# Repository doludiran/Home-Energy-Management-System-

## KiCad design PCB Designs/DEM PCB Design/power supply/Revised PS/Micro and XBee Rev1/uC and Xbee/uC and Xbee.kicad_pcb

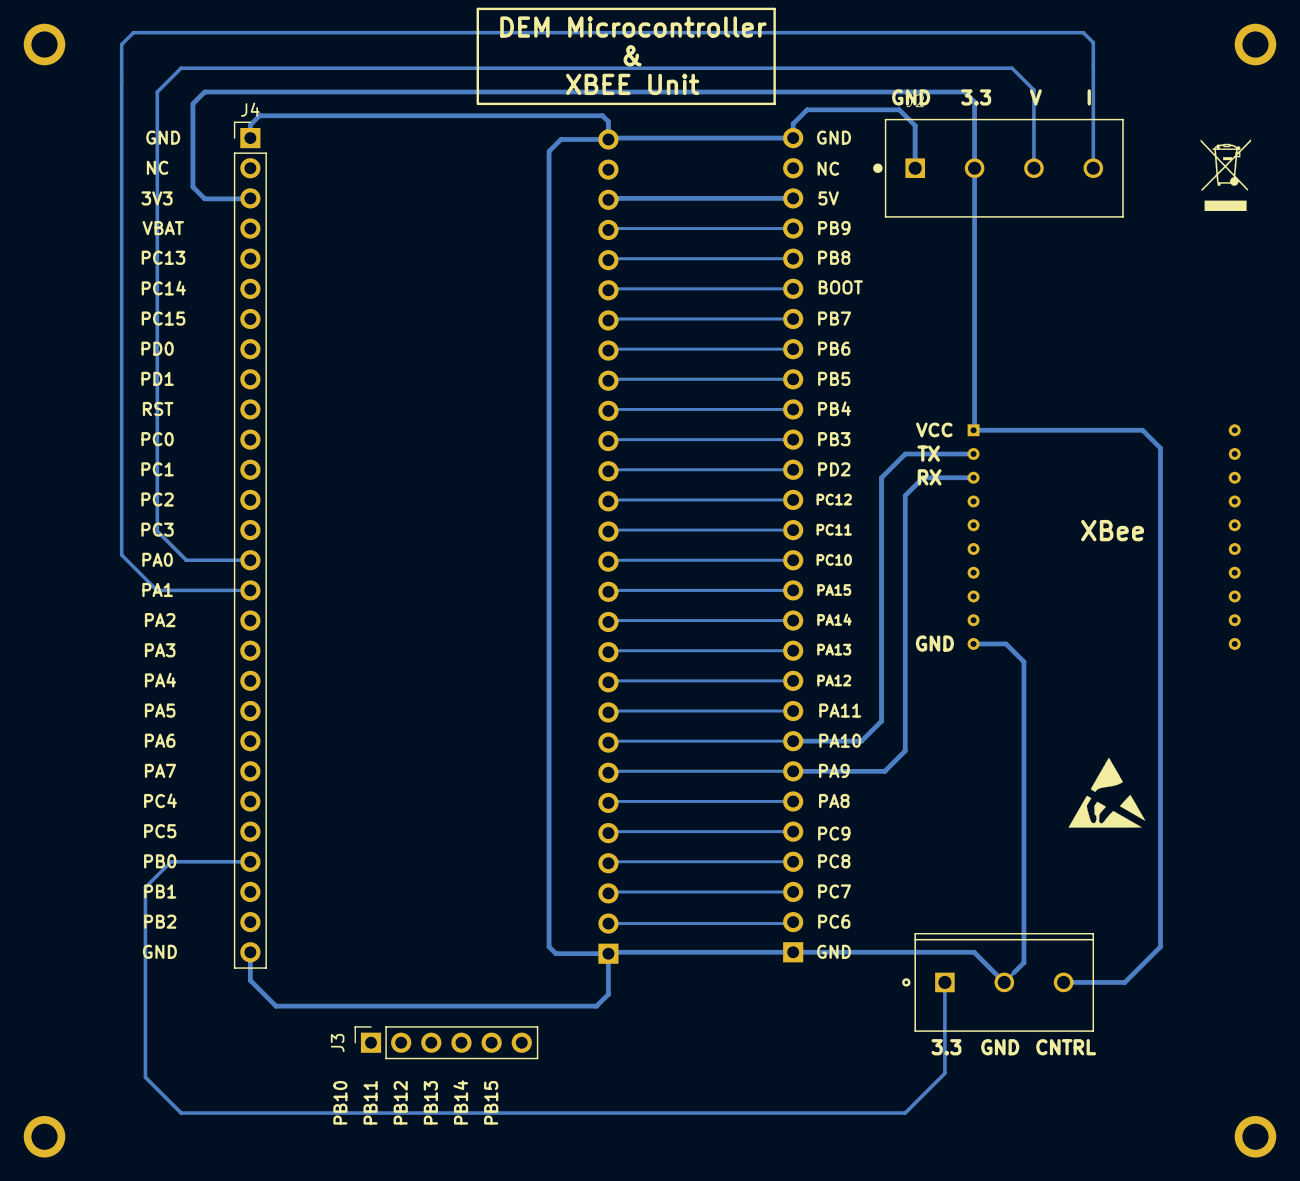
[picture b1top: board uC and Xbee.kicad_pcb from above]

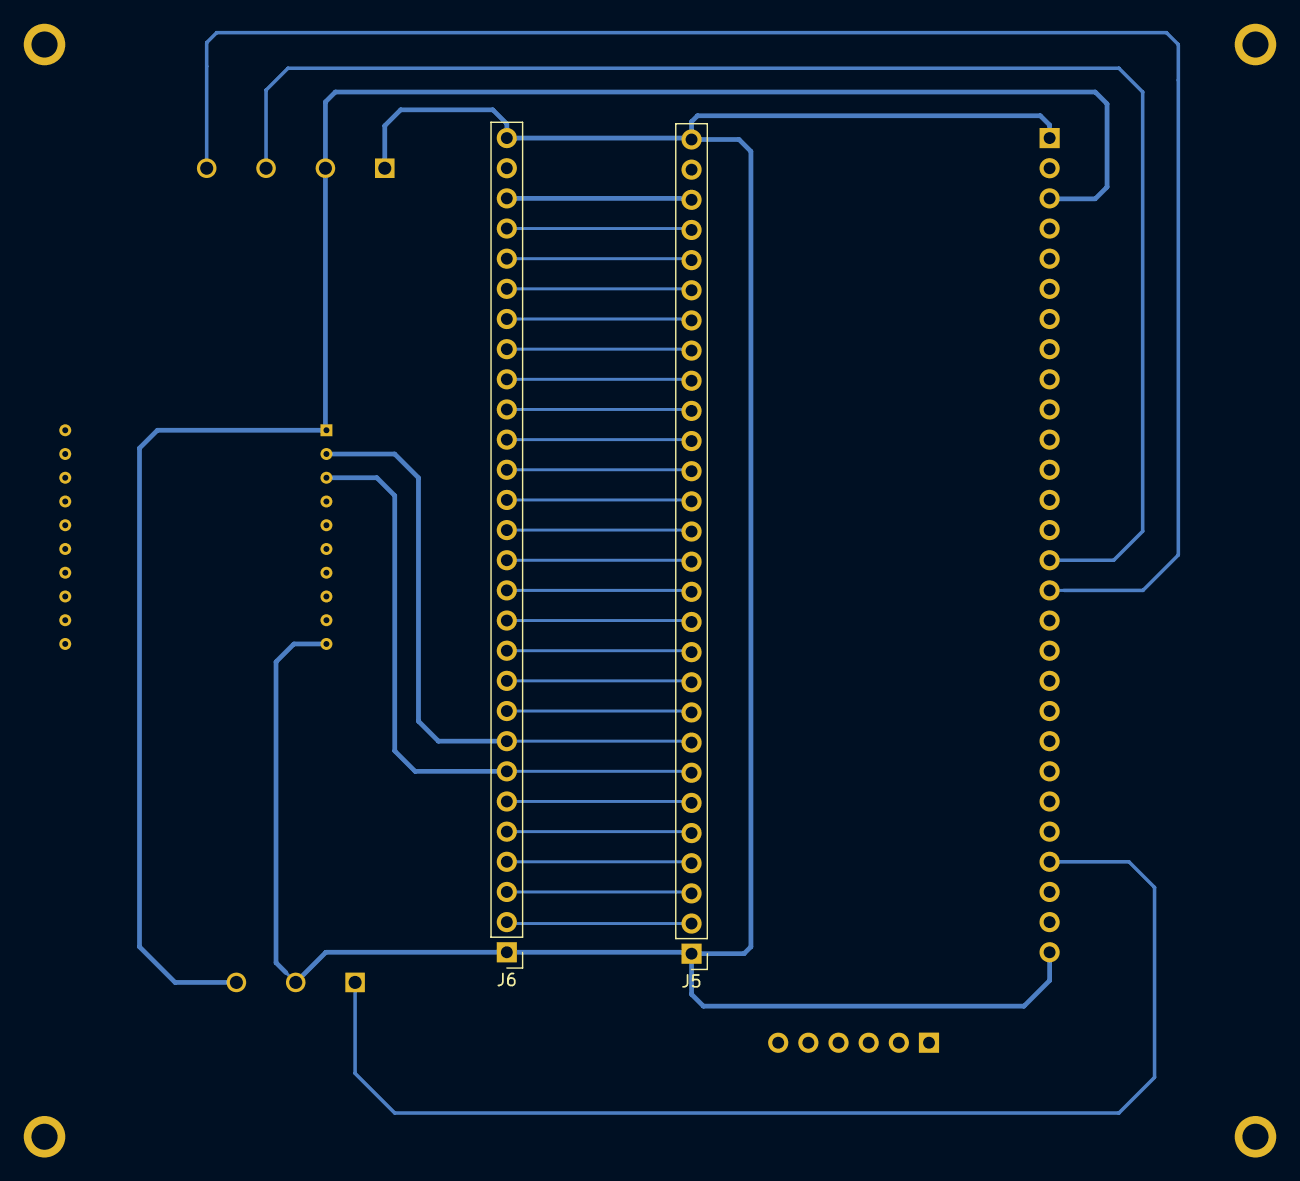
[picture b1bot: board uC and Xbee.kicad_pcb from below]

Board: 2 copper layers, 7 parts (2 on the bottom side), 30 nets.

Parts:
J1: 282836-3; TE_282836-3
J2: 282836-4; TE_282836-4
J3: Conn_01x06_Female; PinSocket_1x06_P2.54mm_Vertical
J4, J5, J6: Conn_01x28_Female; PinHeader_1x28_P2.54mm_Vertical
U1: XB24CDMSIT-001; DIP-20

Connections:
3.3V1: J1.3, J2.2, J4.3, U1.1
5V: J5.26, J6.26
BOOT: J5.23, J6.23
GND1: J1.2, J2.1, J4.1, J4.28, J5.1, J5.28, J6.1, J6.28, U1.10
PA0: J2.3, J4.15
PA1: J2.4, J4.16
PA8: J5.6, J6.6
PA9: J5.7, J6.7, U1.3
PA10: J5.8, J6.8, U1.2
PA11: J5.9, J6.9
PA12: J5.10, J6.10
PA13: J5.11, J6.11
PA14: J5.12, J6.12
PA15: J5.13, J6.13
PB0: J1.1, J4.25
PB3: J5.18, J6.18
PB4: J5.19, J6.19
PB5: J5.20, J6.20
PB6: J5.21, J6.21
PB7: J5.22, J6.22
PB8: J5.24, J6.24
PB9: J5.25, J6.25
PC6: J5.2, J6.2
PC7: J5.3, J6.3
PC8: J5.4, J6.4
PC9: J5.5, J6.5
PC10: J5.14, J6.14
PC11: J5.15, J6.15
PC12: J5.16, J6.16
PD2: J5.17, J6.17

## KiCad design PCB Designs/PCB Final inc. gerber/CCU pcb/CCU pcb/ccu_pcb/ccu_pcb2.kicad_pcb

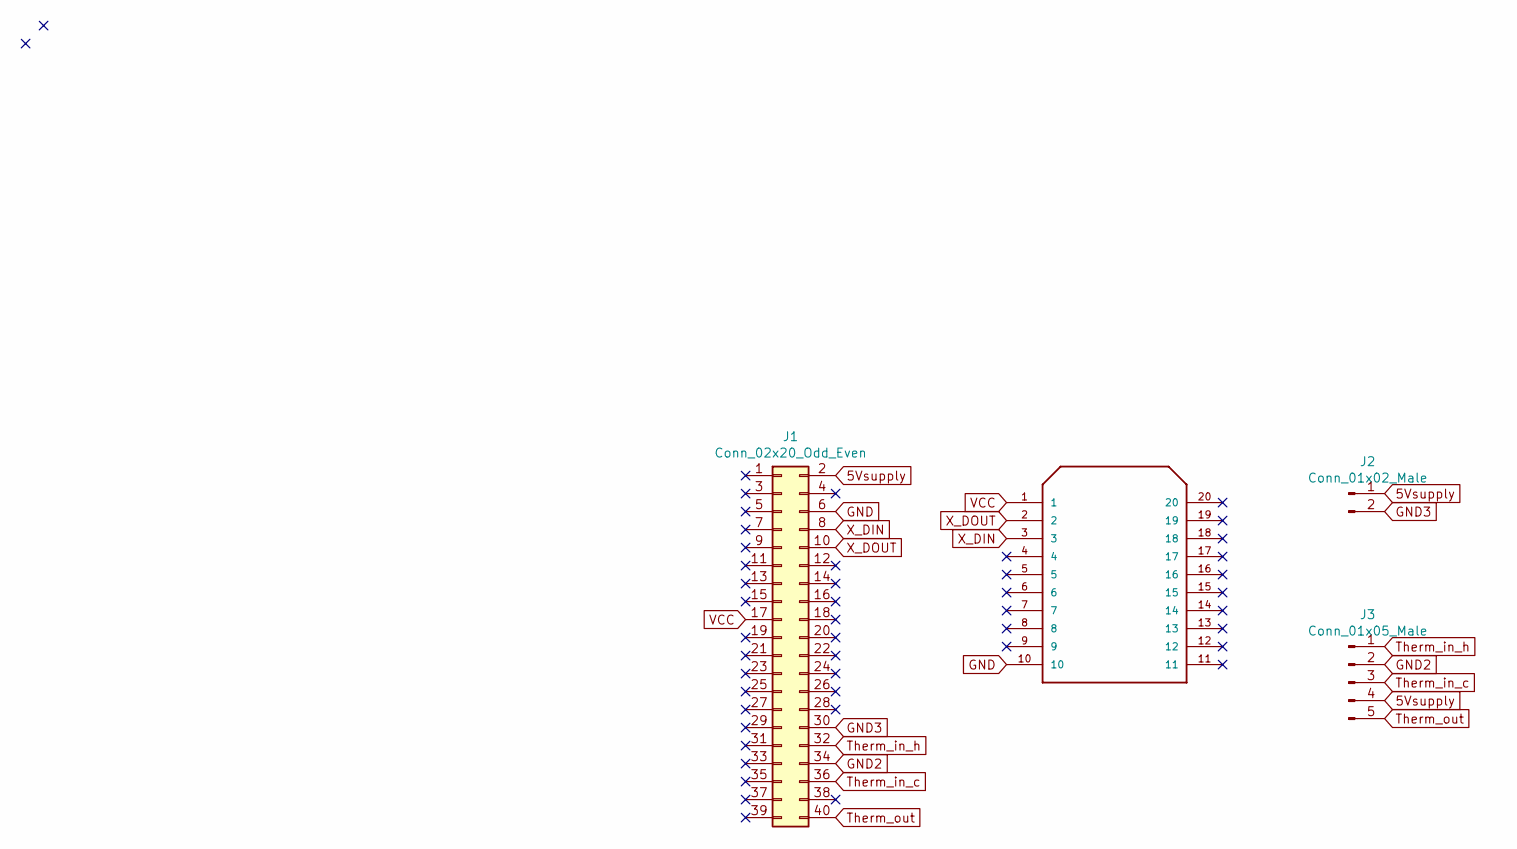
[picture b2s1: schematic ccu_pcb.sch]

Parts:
J1: Conn_02x20_Odd_Even; PinHeader_2x20_P2.54mm_Vertical
J2: Conn_01x02_Male; PinHeader_1x02_P2.54mm_Vertical
J3: Conn_01x05_Male; PinHeader_1x05_P2.54mm_Vertical
U1: XB24CDMPIT-001; DIP-20

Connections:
5Vsupply: J1.2, J2.1, J3.4
GND: J1.6, U1.10
GND2: J1.34, J3.2
GND3: J1.30, J2.2
Therm_in_c: J1.36, J3.3
Therm_in_h: J1.32, J3.1
Therm_out: J1.40, J3.5
VCC: J1.17, U1.1
X_DIN: J1.8, U1.3
X_DOUT: J1.10, U1.2

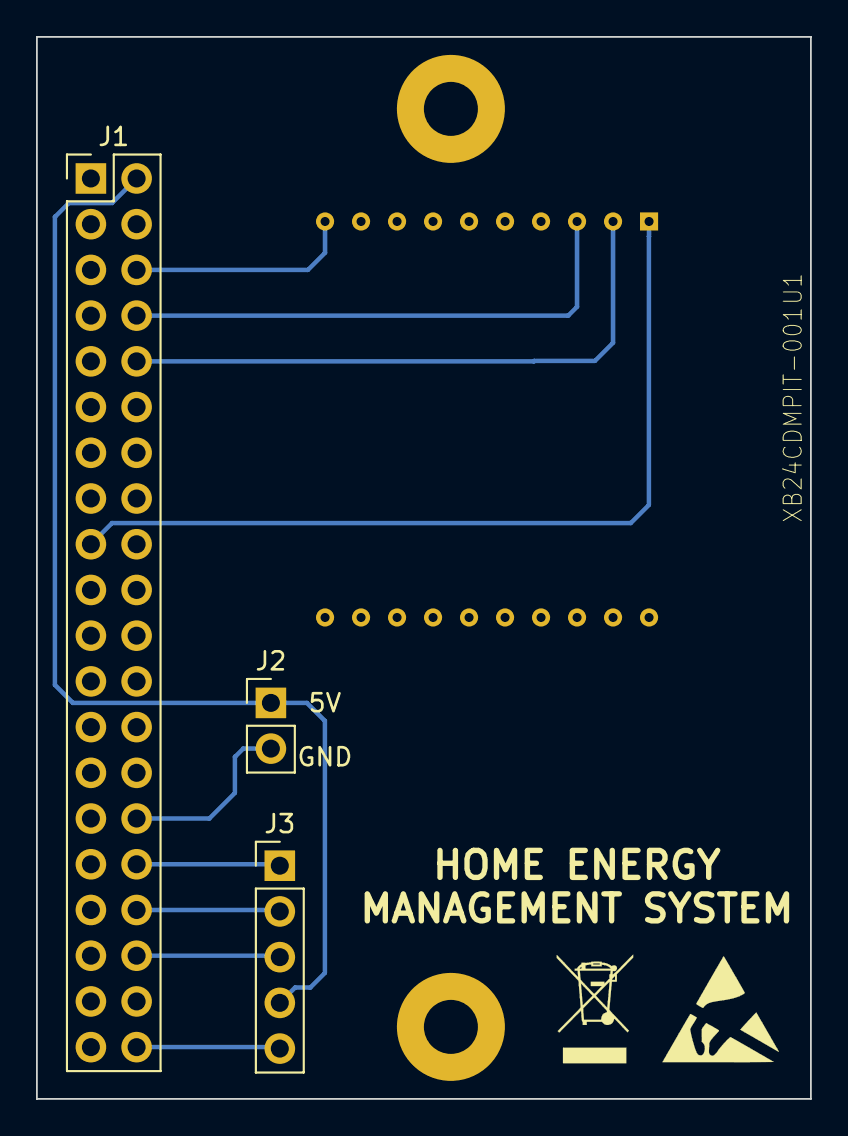
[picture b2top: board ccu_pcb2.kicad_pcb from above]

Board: 2 copper layers, 43.0 x 59.0 mm, 4 parts (0 on the bottom side), 10 nets.

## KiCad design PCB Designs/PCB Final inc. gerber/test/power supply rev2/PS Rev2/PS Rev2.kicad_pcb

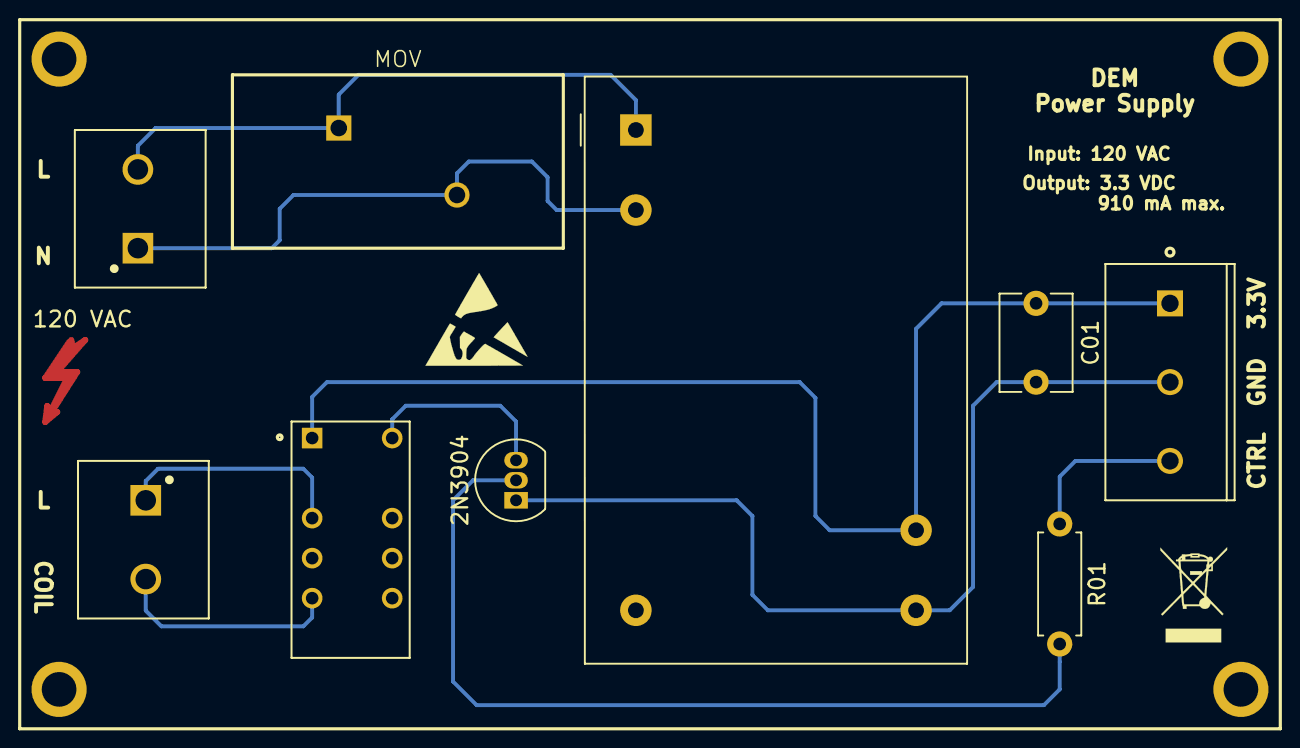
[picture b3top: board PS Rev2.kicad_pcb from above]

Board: 2 copper layers, 10 parts (0 on the bottom side), 9 nets.

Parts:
2N3904: 2N3904; TO-92_Inline
120 VAC : Symbol_Highvoltage_Type1_CopperTop_Small
C01: 400 nF; C_Disc_D6.0mm_W4.4mm_P5.00mm
J01, J03: 1935161; PHOENIX_1935161
J02: 282836-3; TE_282836-3
K01: EC2-3NU; KEMET_EC2-3NU
MOV: TMOV20RP300E; CAPRR750W81L2100T1100H2300P
PS01: RAC03-3.3SGA; Converter_ACDC_RECOM_RAC04-xxSGx_THT
R01: 10k; R_Axial_DIN0207_L6.3mm_D2.5mm_P7.62mm_Horizontal

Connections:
unnamed: C01.1, J02.1, K01.1, PS01.5
unnamed: 2N3904.1, C01.2, J02.2, PS01.4
unnamed: J01.1, MOV.2, PS01.2
unnamed: J01.2, MOV.1, PS01.1
unnamed: J02.3, R01.1
unnamed: J03.1, K01.3
unnamed: J03.2, K01.5
unnamed: 2N3904.3, K01.12
unnamed: 2N3904.2, R01.2
